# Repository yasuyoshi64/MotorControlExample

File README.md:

# sdkconfig
Serial flasher config

	Flash size				4MB

Partition Table

	Patition Table			Single factory app (large), no OTA

MotorControlExample

	LED GPIO number			5

SD card PIN configuration

	MOSI GPIO number		17
	MOSO GPIO number		19
	CLK GPIO number			18
	CS GPIO number			16
	SD card sw GPIO number	4

OLED(SSD1306) PIN configuration

	I2C SDA GPIO number		21
	I2C SCL GPIO number		22

MOTOR(BD65496) PIN configuration

	INA GPIO NUMBER			12
	INB GPIO NUMBER			13

HTTP Server

	WebSocket server support	TRUE

FAT Filesystem support

	Long filename support	Long filename buffer in heap
	OEM Code Page			Japanese (DBCS) (CP932)

Color settings

	Color depth.			1: 1 byte per pixel

Font usage

Enable built-in fonts

	Enable UNSCII 8 (Perfect monospace font)	TRUE

3rd Party Libraries

	QR code library			TRUE

# 機能

## SDカードの内容

### ./config

```
ssid=[Wi-Fi SSID]
pass=[Wi-Fi Password]
```

### ./document

ここにはWeb用のファイルを格納します。

## 使い方

* 「No file」と表示されている場合はSDカードを挿入します。
* 「Wi-Fi Connecting」はWi-Fi接続中です。
* Wi-Fi接続完了後はQRコードが表示されます。QRコードを読み込むとWebのURLが読み込まれ、documentのWebが表示されます。
* QRコードは30秒で消灯します。GPIO0のボタンを押下すると再度30秒表示されます。
* SDカードは電源ON中でも抜き差し可能です。

FA-130モーターは無負荷で70%くらいから回転を始めます。一度回転を始めれば40%くらいまで落としても回転します。
60% = 9000RPM ～　100% = 19000RPM

## 回路図

## Web画面

スライダーを動かすことでモーターを操作できます。
Saveボタンは何も機能しません。

# _Sample project_

(See the README.md file in the upper level 'examples' directory for more information about examples.)

This is the simplest buildable example. The example is used by command `idf.py create-project`
that copies the project to user specified path and set it's name. For more information follow the [docs page](https://docs.espressif.com/projects/esp-idf/en/latest/api-guides/build-system.html#start-a-new-project)

## How to use example
We encourage the users to use the example as a template for the new projects.
A recommended way is to follow the instructions on a [docs page](https://docs.espressif.com/projects/esp-idf/en/latest/api-guides/build-system.html#start-a-new-project).

## Example folder contents

The project **sample_project** contains one source file in C language [main.c](main/main.c). The file is located in folder [main](main).

ESP-IDF projects are built using CMake. The project build configuration is contained in `CMakeLists.txt`
files that provide set of directives and instructions describing the project's source files and targets
(executable, library, or both). 

Below is short explanation of remaining files in the project folder.

```
├── CMakeLists.txt
├── main
│   ├── CMakeLists.txt
│   └── main.c
└── README.md                  This is the file you are currently reading
```
Additionally, the sample project contains Makefile and component.mk files, used for the legacy Make based build system. 
They are not used or needed when building with CMake and idf.py.

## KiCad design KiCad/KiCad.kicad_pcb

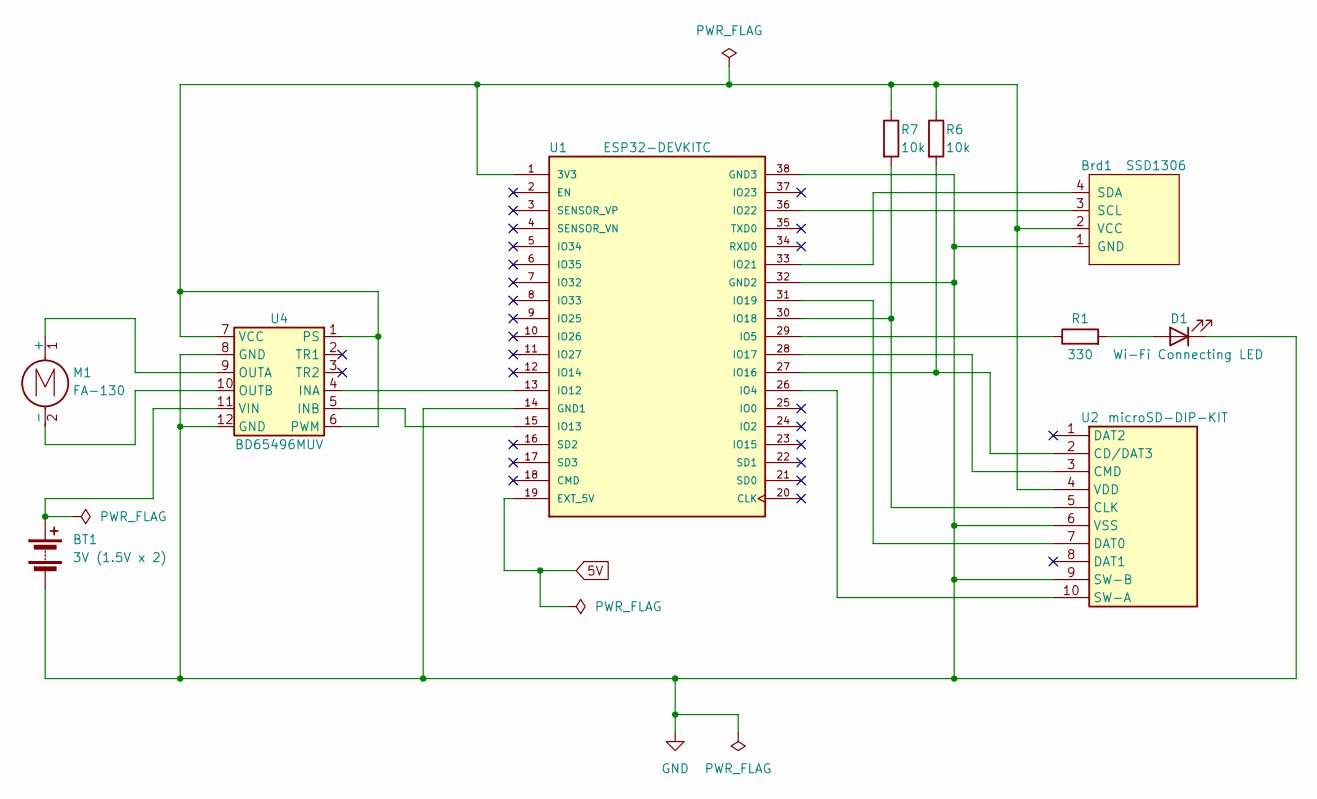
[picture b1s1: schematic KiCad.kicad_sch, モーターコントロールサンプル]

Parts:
BT1: 3V (1.5V x 2); PinHeader_1x02_P1.27mm_Vertical
Brd1: SSD1306; 128x64OLED
D1: Wi-Fi Connecting LED; LED_D5.0mm
M1: FA-130; PinHeader_1x02_P1.27mm_Vertical
R1: 330; R_Axial_DIN0204_L3.6mm_D1.6mm_P5.08mm_Horizontal
R6, R7: 10k; R_Axial_DIN0204_L3.6mm_D1.6mm_P5.08mm_Horizontal
U1: ESP32-DEVKITC; MODULE_ESP32-DEVKITC; PARTREV N/A
U2: microSD-DIP-KIT; microSD-DIP-Kit
U4: BD65496MUV

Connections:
5V: U1.19 (EXT_5V)
GND: BT1.2 (-), Brd1.1 (GND), D1.1 (K), U1.14 (GND1), U1.32 (GND2), U1.38 (GND3), U2.6 (VSS), U2.9 (SW-B), U4.8 (GND), U4.12 (GND)
unnamed: BT1.1 (+), U4.11 (VIN)
unnamed: Brd1.3 (SCL), U1.36 (IO22)
unnamed: Brd1.4 (SDA), U1.33 (IO21)
unnamed: Brd1.2 (VCC), R6.1, R7.1, U1.1 (3V3), U2.4 (VDD), U4.1 (PS), U4.6 (PWM), U4.7 (VCC)
unnamed: D1.2 (A), R1.2
unnamed: M1.1 (+), U4.9 (OUTA)
unnamed: M1.2 (-), U4.10 (OUTB)
unnamed: U1.26 (IO4), U2.10 (SW-A)
unnamed: R1.1, U1.29 (IO5)
unnamed: U1.13 (IO12), U4.4 (INA)
unnamed: U1.15 (IO13), U4.5 (INB)
unnamed: R6.2, U1.27 (IO16), U2.2 (CD/DAT3)
unnamed: U1.28 (IO17), U2.3 (CMD)
unnamed: R7.2, U1.30 (IO18), U2.5 (CLK)
unnamed: U1.31 (IO19), U2.7 (DAT0)

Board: 2 copper layers, 10 parts (0 on the bottom side), 16 nets, no tracks yet.

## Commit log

2024-03-11 初期コミット
2024-03-16 モーターコントロールを追加
2024-03-16 PWMピンの意味を勘違いしてて修正
2024-03-21 画像追加
2024-03-21 説明追加
2024-04-17 モーター2個に増量
2024-04-17 KiCadの回路図追加
2024-04-17 ミスった
2024-04-18 BD65496MUVのPWMをLOWへ
2024-04-19 BD65496MUVをEN/INモードで動作するように変更
